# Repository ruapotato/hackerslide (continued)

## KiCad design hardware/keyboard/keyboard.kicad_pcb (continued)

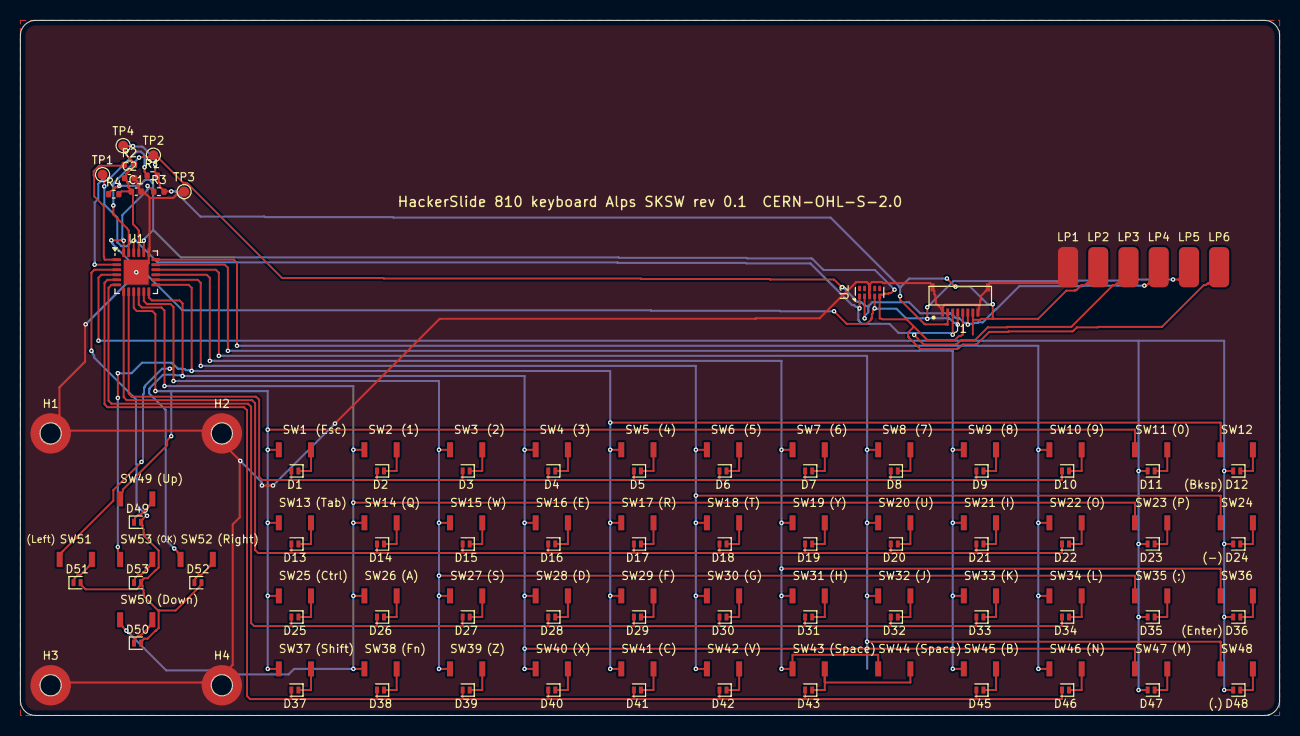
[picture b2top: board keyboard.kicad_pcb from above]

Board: 2 copper layers, 125.0 x 69.0 mm, 128 parts (0 on the bottom side), 76 nets.

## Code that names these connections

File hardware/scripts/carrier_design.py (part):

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# Debug UART on a 3-pin JST-SH, GND in the middle.
# Pin order from the Raspberry Pi 3-pin Debug Connector Specification (RP-008189-DS): 1 = RX into the target,
# 2 = GND, 3 = TX out of the target; 100 ohm in series at the target.
UART_PINS = {'1': 'UART_DBG_RX', '2': 'GND', '3': 'UART_DBG_TX'}
UART_NOTE = 'Raspberry Pi debug-probe pinout: 1=RX (into SoC) 2=GND 3=TX (from SoC)'


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                        '26 AWG leads: crimp them into a Molex 5264 3-way housing (5263 terminals), red + at circuit 1 = pin 1 here, '
                        'black - at circuit 3, circuit 2 empty. Put a meter on the '
                        'plug before the first use: reversed, the pack destroys the charger'))
    R(p, 'R68', '0', 'BATT_NTC', 'CHG_TS', dnp=True, note='DNP: only for a pack with its own 10k thermistor on pin 2 (then leave TH1 out)')
    p.add('U4', 'hackerslide', 'MAX17048', 'MAX17048G+T10', 'Package_DFN_QFN:TDFN-8-1EP_2x2mm_P0.5mm_EP0.8x1.2mm',
          {'1': 'GND', '2': 'VBAT', '3': 'VBAT', '4': 'GND', '5': 'GAUGE_INT', '6': 'GND', '7': 'I2C_B_SCL',
           '8': 'I2C_B_SDA', '9': 'GND'},
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                                    'chosen against on stock (118 on 2026-11-26). dVdt (pin 1) open = fastest turn-on'))
    R(p, 'R66', '1.1k', 'BATT_ILIM', 'GND', note='current limit 2000 / 1100 + 0.04 = 1.86 A typ, about 1.73-1.99 A (TI SLVSE57 eq. 4; table: 487R 4.17 A, 1780R 1.17 A, +-7 %): under the 2 A rating of the Jauch pack')
    R(p, 'R67', '10k', 'BATT_OC_N', '+3V3', note='FLT, low while the fuse is in thermal shutdown')
    R(p, 'R90', '10M', 'VSYS', 'FUSE_EN', note='enable: on whenever VSYS is present (threshold 1.2 V, pin leakage 0.1 uA)')
    C(p, 'C90', '2.2u', 'FUSE_EN', dnp=True)               # hard power-cycle option, see the sheet notes
    R(p, 'R91', '1M', 'FUSE_EN', 'FUSE_CUT', dnp=True)
    SCHOTTKY(p, 'D9', 'FUSE_CUT', 'PWR_SW_N', note='DNP: hard power-cycle option', dnp=True)
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    R(p, 'R19', '100k', 'BOOST_FB', 'GND')
    C(p, 'C26', '22p', '+5V', 'BOOST_FB', dnp=True)        # P8: feed-forward pad
    R(p, 'R20', '100k', 'BOOST_PG', '+5V')
    C(p, 'C21', '22u', 'VSYS_LIM')                         # P4: 22 uF at U5 pin 10
    C(p, 'C22', '22u', '+5V')
    C(p, 'C23', '22u', '+5V')
    C(p, 'C24', '22u', '+5V')
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    p.add('SW1', 'Switch', 'SW_Push', 'PWR', 'Button_Switch_SMD:SW_SPST_EVQP7C', {'1': 'PWR_SW_N', '2': 'GND'},
          fields=fields('C388883', 'EVQP7C01P', 'Panasonic', Description='side-actuated power button'))
    SCHOTTKY(p, 'D3', 'CHG_QON_N', 'PWR_SW_N', note='/QON (VIL 0.4 V max: Schottky needed)')
    SCHOTTKY(p, 'D7', 'MOD_PWRON', 'PWR_SW_N', note='module pin 99 through R26')
    SCHOTTKY(p, 'D8', 'PWR_KEY_N', 'PWR_SW_N', note='GPIO power key (gpio-keys, KEY_POWER)')
    R(p, 'R26', '1k', 'MOD_PWRON', 'MOD_PIN99', note='M1: limits current if pin 99 is a driven output')
    R(p, 'R27', '10k', 'PWR_KEY_N', '+3V3')
    for ref, net in (('TP1', 'VBUS'), ('TP2', 'VSYS'), ('TP3', 'VBAT'), ('TP4', '+5V'), ('TP5', 'GND'), ('TP6', 'BOOST_PG'),
                     ('TP7', 'REGN'), ('TP8', 'CHG_TS'), ('TP15', 'CHG_QON_N')):
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        'J1A/J1B: Hirose DF40C-100DS-0.4V (1.5 mm stack). Pin names = Raspberry Pi CM4 datasheet.',
        'Verified pin by pin for LuckFox Core3566 and Radxa CM4 (RK3576): docs/compute-pin-matrix.md.',
        'M4: ArmSoM-CM5 variant: R30, R33, R34 DNP; R35, R36 fitted; backlight PWM and audio NOT supported.',
        'GPIO_VREF (pin 78) = 3.3 V through R30.',
        'USB: the module OTG port goes straight to USB-C (device mode for flashing; ID pin 101 floats).',
        'H1-H4: Wuerth 9774015151R SMT spacers (M2.5, 1.5 mm) soldered on the module side; their 1.4 mm boss',
        'shows 0.4 mm on the display side of the 1.0 mm board (E7).  HS1/HS2: body screw passages, the shell bosses clamp the board here.'])
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        m(pin, '+3V3')
    for pin in (88, 90):
        m(pin, '+1V8')
    m(78, 'GPIO_VREF')
    # display / touch
    m(175, 'DSI_D0_N'); m(177, 'DSI_D0_P'); m(181, 'DSI_D1_N'); m(183, 'DSI_D1_P'); m(187, 'DSI_CLK_N'); m(189, 'DSI_CLK_P')
    m(80, 'I2C_A_SCL'); m(82, 'I2C_A_SDA')
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    m(37, 'KB_INT_N'); m(45, 'KB_RST_N')
    # buttons, slider, LED, jack detect
    m(38, 'VOL_UP_N'); m(39, 'VOL_DN_N'); m(47, 'SLIDE_DET_R'); m(21, 'LED_ACT_N'); m(41, 'PWR_KEY_N'); m(50, 'HP_DET_SOC')
    m(99, 'MOD_PIN99'); m(92, 'RUN_PG'); m(93, 'NRPIBOOT')
    # USB
    m(101, 'USB_OTG_ID'); m(103, 'USB_DM'); m(105, 'USB_DP')
    # SD card (CM4Lite-style SD signals)
    m(57, 'SD_CLK'); m(62, 'SD_CMD'); m(63, 'SD_D0'); m(67, 'SD_D1'); m(69, 'SD_D2'); m(61, 'SD_D3'); m(76, 'SD_CD_N')
    # debug UART (CM4 GPIO14/15 = Core3566 UART2, Radxa UART0) + ArmSoM alternative on 54/56
    m(55, 'UART_TX'); m(51, 'UART_RX'); m(54, 'CM4_GPIO4'); m(56, 'CM4_GPIO3')
    # audio I2S candidates (resistor-selected per module family, see audio sheet)
    m(25, 'CM4_GPIO21'); m(26, 'CM4_GPIO19'); m(27, 'CM4_GPIO20'); m(29, 'CM4_GPIO16'); m(30, 'CM4_GPIO6'); m(49, 'CM4_GPIO18')
    m(44, 'CODEC_IRQ')
    m(58, 'BATT_OC_N')   # battery discharge limiter FAULT (was the spare pin)
    from mklib import CM4
    for pin, name in CM4.items():
        if name == 'GND':
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    for i in range(2):
        mo.add(f'HS{i + 1}', 'Mechanical', 'MountingHole', 'M2 body screw', 'hackerslide:MountingHole_M2_NPTH_BodyScrew', {},
               in_bom=False)
    R(mo, 'R30', '0', '+3V3', 'GPIO_VREF', note='GPIO bank at 3.3 V. DNP for ArmSoM-CM5 (pin 78 = VRTC)')
    C(mo, 'C30', '100n', 'GPIO_VREF')
    C(mo, 'C37', '1u', 'GPIO_VREF')                        # M10
    C(mo, 'C33', '100n', '+5V')                            # at the module 5 V pins; bulk is C22-C24 at the boost, 8 mm away
    C(mo, 'C34', '100n', '+5V')
    C(mo, 'C35', '10u', '+3V3')
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    mo.add('J8', 'Connector', 'Conn_01x03_Pin', 'DEBUG UART', 'Connector_JST:JST_SH_SM03B-SRSS-TB_1x03-1MP_P1.00mm_Horizontal',
           UART_PINS, fields=fields('C160403', 'SM03B-SRSS-TB(LF)(SN)', 'JST',
                                    Description='A6: side entry. ' + UART_NOTE + ', 3.3 V'))
    R(mo, 'R33', '100', 'UART_TX', 'UART_DBG_TX', note='CM4 GPIO14 / Core3566 UART2 TX (1.5 Mbaud)')
    R(mo, 'R34', '100', 'UART_RX', 'UART_DBG_RX', note='CM4 GPIO15 / Core3566 UART2 RX')
    R(mo, 'R35', '100', 'CM4_GPIO4', 'UART_DBG_TX', dnp=True, note='ArmSoM-CM5 UART0 TX on pin 54')
    R(mo, 'R36', '100', 'CM4_GPIO3', 'UART_DBG_RX', dnp=True, note='ArmSoM-CM5 UART0 RX on pin 56')
    # bring-up aids: pads on the debug UART for a plain 3.3 V USB-serial adapter (no JST-SH lead needed), pads on
    # the system I2C bus, and a lamp on +5V that shows charger, fuse and boost are all passing power
    for net, ref in (('UART_DBG_TX', 'TP34'), ('UART_DBG_RX', 'TP35'), ('I2C_B_SCL', 'TP36'), ('I2C_B_SDA', 'TP37')):
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        'ES8316 (mainline snd-soc-es8316). AVDD/PVDD 3.3 V, DVDD/CPVDD 1.8 V. CE low: I2C address 0x10. MCLK is mandatory.',
        'Capacitors per the Everest application circuit (datasheet p.4), incl. 1u on MICBIAS and CPVDD (A4).',
        'I2S straps: fit R50-R54 for LuckFox Core3566 (I2S3_M1), or R55-R59 for the CM4 PCM pinout (Radxa CM4 SAI2).',
        'Jack PJ-342: tip switch (terminal 4) -> HP_DET (ES8316 GPIO1 and module pin 50). Mic contact -> GPIO2 via 15k (A5).',
        'A7: the PJ-342 pole assignment of terminals 2 and 5 is inferred from the drawing. R60/R61 fitted = CTIA with',
        '    terminal 5 = sleeve (mic). Swap to R62/R63 if a sample shows terminal 2 is the sleeve (or for OMTP headsets).',
        'A8: CPGNDREF senses the jack ground: HPGND joins GND only through R49, placed at the jack.'])
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    R(au, 'R46', '33', 'HP_L', 'JACK_T', note='A4: datasheet value')
    R(au, 'R47', '33', 'HP_R', 'JACK_R1')
    R(au, 'R48', '10k', 'HP_DET', '+3V3', note='A5: low while the tip switch is closed (no plug)')
    R(au, 'R69', '10k', 'HP_DET', 'HP_DET_C', note='with no plug HP_DET follows HP_L, which swings below ground: limits the current into GPIO1')
    R(au, 'R64', '1k', 'HP_DET', 'HP_DET_SOC', note='same signal to a module GPIO (ES8316 IRQ behaviour unverified)')
    R(au, 'R65', '15k', 'MIC_SLEEVE', 'MIC_DET', note='A5: headset mic / button detect (ES8316 GPIO2)')
    R(au, 'R49', '0', 'HPGND', 'GND', note='A8: single ground join, at the jack')
    au.add('J6', 'hackerslide', 'PJ-342', 'PJ-342', 'hackerslide:Jack_3.5mm_SHOUHAN_PJ-342',
           {'3': 'JACK_T', '4': 'HP_DET', '6': 'JACK_R1', '2': 'JACK_P2', '5': 'JACK_P5'},
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    TVS(au, 'D10', 'JACK_T')
    TVS(au, 'D11', 'JACK_R1')
    TVS(au, 'D12', 'MIC_SLEEVE')
    straps_a = [('R50', '33', 'I2S_MCLK', 'CM4_GPIO21'), ('R51', '33', 'I2S_SCLK', 'CM4_GPIO20'), ('R52', '0', 'I2S_LRCK', 'CM4_GPIO6'),
                ('R53', '0', 'I2S_DACDAT', 'CM4_GPIO19'), ('R54', '0', 'I2S_ADCDAT', 'CM4_GPIO18')]
    straps_b = [('R55', '33', 'I2S_MCLK', 'CM4_GPIO16'), ('R56', '33', 'I2S_SCLK', 'CM4_GPIO18'), ('R57', '0', 'I2S_LRCK', 'CM4_GPIO19'),
                ('R58', '0', 'I2S_DACDAT', 'CM4_GPIO21'), ('R59', '0', 'I2S_ADCDAT', 'CM4_GPIO20')]
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
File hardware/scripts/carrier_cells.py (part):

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        x, y = c.rel('U3', pin)
        k = 0.6 / max(abs(x), abs(y))
        c.T('GND', [(x, y), (x * k, y * k)], 0.25)
    # PMID: C11 directly at pin 23, C12 beside it on the same copper; ground ends two vias away from the plane
    c.P('C11', 4.4, -1.75, 0)
    c.P('C12', 4.4, -3.75, 0)
    c.T('PMID', [('U3', '23'), (2.7, -0.75), (3.45, -1.35)], 0.25)
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    c.P('C14', 5.0, 0.85, -90)
    c.T('REGN', [('U3', '22'), (4.3, -0.25), ('C14', '1')], 0.15)
    c.gnd('C14', '2', 0.0, 1.1)
    # SYS: pins 15/16 straight down into L1 pad 2; C15/C16 below the inductor; vias into the In2 VSYS area
    c.T('VSYS', [(0.0, 1.96), (0.0, 2.9), (-0.5, 3.5), (-0.5, 4.8)], 0.6)
    c.P('C15', -0.3, 9.6, -90)
    c.P('C16', 1.7, 9.6, -90)
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
    # ---- signal pins ------------------------------------------------------------------------------------
    # left side: stubs under the module edge to vias; their parts are on the display side below the spacer H2
    for pin, net, vx in (('7', 'CHG_INT_N', -4.2), ('10', 'CHG_ILIM', -4.2), ('11', 'CHG_TS', -4.8), ('12', 'CHG_QON_N', -4.2)):
        x, y = c.rel('U3', pin)
        c.T(net, [(x, y), (vx, y)], 0.15)
        c.V(net, vx, y, 0.45, 0.2)
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    c.P('TP3', -2.5, -7.5, 0, 'B')                        # VBAT, inside the VBAT copper

    # ---- battery fuse U13 (TPS259531, 2 x 2 mm) on the display side, straight under the VSYS vias --------------
    # turned so that IN (pins 3, 4) faces the vias and OUT (pin 5) faces the In2 VSYS_LIM area:
    #   top row    dVdt  EN  IN  IN        bottom row    GND  ILM  FLT  OUT
    c.P('U13', 3.8, 10.3, 270, 'B')
    c.T('VSYS', [(4.1, 8.65), (4.9, 8.65)], 0.6, Bk)
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        px, py = c.rel('U4', pin)
        c.T('GND', [(px, py), (px, py * 0.6), (px * 0.5, py * 0.3)], 0.2, Bk)
    c.V('GND', 0.0, 0.0, 0.45, 0.2)                       # in the exposed pad
    for pin, net, vy in (('5', 'GAUGE_INT', 1.9), ('7', 'I2C_B_SCL', 1.9), ('8', 'I2C_B_SDA', 2.5)):
        px, py = c.rel('U4', pin)
        c.T(net, [(px, py), (px, vy)], 0.15, Bk)
        c.V(net, px, vy, 0.45, 0.2)
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    c.T('BOOST_SW', [('U5', '1'), (1.0, -2.0)], 0.25)
    c.T('BOOST_SW', [('U5', '2'), (0.5, -2.0)], 0.25)
    c.T('BOOST_SW', [(0.5, -2.0), (3.6, -2.0)], 0.5)
    # VIN: pin 10 -> L2 pad 1, C21, three vias into the In2 VSYS_LIM area
    c.T('VSYS_LIM', [(1.0, 1.7), (1.4, 2.1), (3.6, 2.1)], 0.4)
    c.two('C21', 3.9, 4.85, 'L')
    c.T('VSYS_LIM', [(2.91, 2.1), (2.91, 4.5)], 0.4)
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    """SD_D0 and SD_D2 from their J1A fan-out vias to the fan-out vias of the ESD arrays U11/U12, on the display
    side.  These two pins sit at the crowded end of the J1A via field and the router could not get them out once
    their neighbours were in; laid first, the router works around them.  The other SD lines are routed by it."""
    for net, ref, pin, lane in (('SD_D0', 'U11', '4', 54.1), ('SD_D2', 'U12', '1', 55.4)):
        vx, vy = B.via_xy(net, (40.5, 52.0))
        tx, ty = B.via_xy(net, B.pad_xy(ref, pin))
        k = abs(lane - ty)
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
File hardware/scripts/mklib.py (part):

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    # ES8316 (Everest datasheet rev 6.0, pin table section 2)
    out.append(box_symbol('ES8316', [
        ('1', 'CCLK', I), ('32', 'CDATA', B), ('31', 'CE', I), None, ('2', 'MCLK', I), ('6', 'SCLK', B),
        ('8', 'DLRCK', B), ('7', 'DSDIN', I), ('9', 'ASDOUT', O), None, ('10', 'GPIO1', B), ('11', 'GPIO2', B),
        ('12', 'GPIO3', B), None, ('3', 'DVDD', PI), ('4', 'PVDD', PI), ('22', 'AVDD', PI), ('14', 'CPVDD', PI)],
        [('20', 'LOUT', O), ('19', 'ROUT', O), None, ('30', 'LIN1', I), ('29', 'RIN1', I), ('28', 'LIN2', I),
         ('27', 'RIN2', I), ('26', 'MICBIAS', PO), None, ('21', 'DACVREF', P), ('24', 'ADCVREF', P), ('25', 'VMID', P),
         ('15', 'CPTOP', P), ('16', 'CPBOT', P), ('13', 'CPVSSP', P), ('18', 'CPGNDREF', P), None,
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                          descr='TI TPS61169 white-LED boost driver, 38 V switch, FB 204 mV',
                          footprint='Package_TO_SOT_SMD:SOT-353_SC-70-5',
                          datasheet='https://www.ti.com/lit/ds/symlink/tps61169.pdf'))
    # TCA8418 (TI SCPS215G, RTW pin table): pins 1-8 = ROW7..ROW0, 9-18 = COL0..COL9
    out.append(box_symbol('TCA8418RTW',
        [('22', 'SDA', B), ('23', 'SCL', I), ('24', '~{INT}', 'open_collector'), ('20', '~{RESET}', I), None,
         ('21', 'VCC', PI), ('19', 'GND', PI), ('25', 'EP', P)] + [None] * 2,
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
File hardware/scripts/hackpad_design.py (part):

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        R(k, f'R{30 + i}', '10k', f'BT_CFG{i}', 'GND')
    pad('GPIO_LPSR_14', 'SWD_CLK'); pad('GPIO_LPSR_15', 'SWD_DIO'); pad('GPIO_LPSR_13', 'JTAG_MOD')
    R(k, 'R24', '4.7k', 'JTAG_MOD', 'GND', note='HDUG: pull down')
    pad('GPIO_AD_24', 'UART_DBG_TX'); pad('GPIO_AD_25', 'UART_DBG_RX')
    k.add('J1', 'Connector', 'Conn_01x03_Pin', 'DEBUG_UART', 'Connector_JST:JST_SH_SM03B-SRSS-TB_1x03-1MP_P1.00mm_Horizontal',
          {'1': 'UART_DBG_RX', '2': 'GND', '3': 'UART_DBG_TX'},
          fields=fields('C160403', 'SM03B-SRSS-TB(LF)(SN)', 'JST', Description='Raspberry Pi debug-probe pin order: 1 = into the board'))
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        use(net)
    au.add('U18', 'hackerslide', 'ES8316', 'ES8316', 'Package_DFN_QFN:VQFN-32-1EP_4x4mm_P0.4mm_EP2.8x2.8mm',
           {'1': 'I2C_U_SCL', '32': 'I2C_U_SDA', '31': 'GND', '2': 'BT_CFG9', '6': 'AUD_BCLK', '8': 'AUD_LRCK', '7': 'AUD_DAC',
            '9': 'AUD_ADC', '10': 'HP_DET', '11': 'CODEC_GPIO2', '12': 'CODEC_IRQ', '3': '+1V8', '4': '+3V3', '22': 'AVDD_CODEC',
            '14': '+1V8', '20': 'HP_L', '19': 'HP_R', '30': 'MIC_P', '29': 'MIC_N', '26': 'MICBIAS', '21': 'DACVREF', '24': 'ADCVREF',
            '25': 'VMID', '15': 'CPTOP', '16': 'CPBOT', '13': 'CPVSSP', '18': 'HPGND', '5': 'GND', '23': 'GND', '17': 'GND', '33': 'GND'},
           fields=fields('C365735', 'ES8316', 'Everest Semiconductor'))
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    C(au, 'C242', '1u', 'MIC_P', 'HPGND'); C(au, 'C243', '1u', 'MIC_N', 'HPGND')
    R(au, 'R231', '33', 'HP_L', 'JACK_A'); R(au, 'R232', '33', 'HP_R', 'JACK_B')
    R(au, 'R233', '100k', 'HP_DET', '+3V3', note='jack switch to ground on the other side')
    R(au, 'R234', '100k', 'CODEC_GPIO2', 'GND'); R(au, 'R235', '100k', 'CODEC_IRQ', 'GND')
    R(au, 'R236', '0', 'HPGND', 'GND', note='single ground join, at the jack')
    au.add('J5', 'hackerslide', 'PJ-3528S', 'PJ-3528S', 'hackerslide:Jack_3.5mm_XKB_PJ-3528S_EdgeNotch',
           {'3': 'JACK_A', '2': 'JACK_B', '1': 'HPGND', '5': 'HP_DET', '4': 'GND'},
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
